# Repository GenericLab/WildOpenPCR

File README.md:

# WildOpenPCR
DIY derivate of the OpenPCR Project.
Original design of OpenPCR by Tito Jakowski and Jeff Perfutto: http://openpcr.org/

For more info see: http://wlu18www30.webland.ch/wiki/Wild_OpenPCR

and: http://www.gaudi.ch/GaudiLabs/?page_id=328

All OpenPCR software, design files and instructions are licensed under the GNU GPLv3.

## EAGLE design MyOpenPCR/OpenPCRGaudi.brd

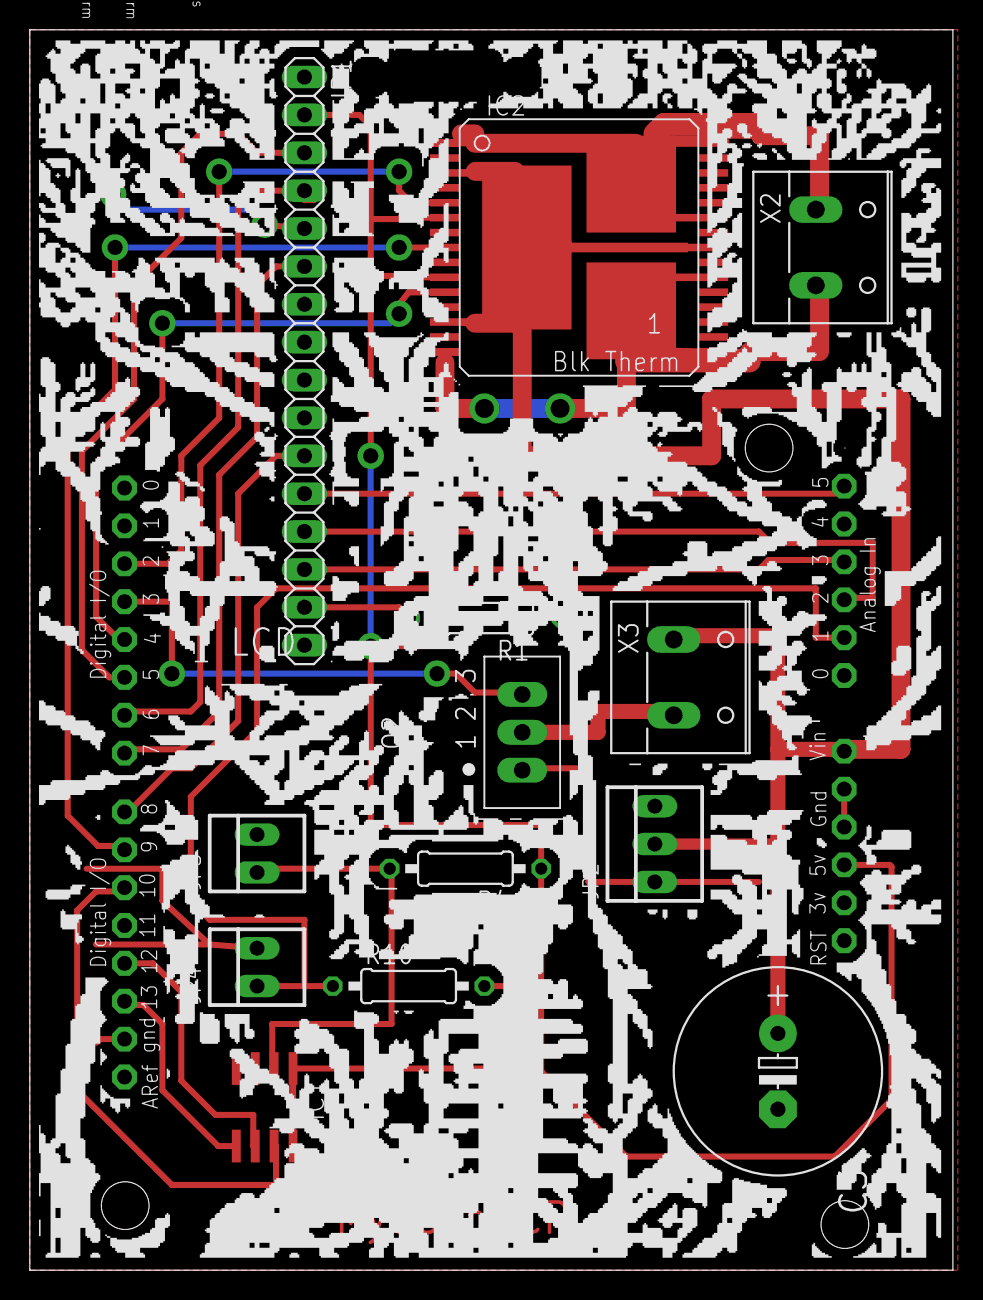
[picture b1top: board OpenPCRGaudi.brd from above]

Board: 2 copper layers, 61.9 x 83.2 mm, 14 parts (0 on the bottom side), 23 nets.

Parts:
C3: E5-13
IC1: MCP3551SN; SO-08
IC2: VNH3SP30_2; MULTIPOWERSO-30
JP1: 1X16
JP2: 22-23-2031
JP3, JP4: 22-23-2021
Q2: BSS97; TO202
R1, R4, R10: 0207/10
U$3: ARDUINODUEMILANOVE; ARDUINO
X2, X3: W237-132

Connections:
+5VREG: IC1.1, IC1.8, IC2.6, IC2.10, JP1.2, R1.1, R4.1, R10.2, U$3.5V
+12V1: C3.+, IC2.3, IC2.13, IC2.23, IC2.VCC, IC2.VCC@1, JP2.2, U$3.VIN, X3.1
GND1: C3.-, IC1.3, IC1.4, IC2.18, IC2.19, IC2.20, IC2.26, IC2.27, IC2.28, JP1.1, JP1.5, JP1.16, JP2.1, JP3.2, JP4.2, Q2.1, U$3.GND, U$3.GND1, U$3.GND2
unnamed: JP1.3, U$3.D5
unnamed: JP1.4, U$3.D6
unnamed: JP1.14, U$3.A3
unnamed: JP1.15, R1.2
unnamed: Q2.3, U$3.D3
unnamed: JP1.13, U$3.A2
unnamed: JP1.6, U$3.D7
unnamed: JP1.12, U$3.A5
unnamed: IC1.5, U$3.D13
unnamed: Q2.2, X3.2
unnamed: JP1.11, U$3.D8
unnamed: IC1.2, JP3.1, R4.2
unnamed: IC2.1, IC2.25, IC2.30, IC2.GND, IC2.OUTA, X2.1
unnamed: IC1.6, U$3.D12
unnamed: IC1.7, U$3.D10
unnamed: IC2.8, U$3.D9
unnamed: IC2.11, U$3.D4
unnamed: IC2.15, IC2.16, IC2.21, IC2.OUTB, IC2.SS, X2.2
unnamed: IC2.5, U$3.D2
unnamed: JP4.1, R10.1, U$3.A1

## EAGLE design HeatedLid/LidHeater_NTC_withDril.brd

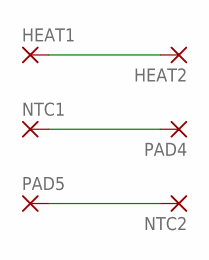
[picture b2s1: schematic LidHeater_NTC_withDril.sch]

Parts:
HEAT1, HEAT2: SMD5; SMD2,54-5,08
NTC1, NTC2: SMD5; SMD2,54-5,08
PAD4, PAD5: SMD5; SMD2,54-5,08

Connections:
unnamed: HEAT1.1, HEAT2.1
unnamed: NTC1.1, PAD4.1
unnamed: NTC2.1, PAD5.1

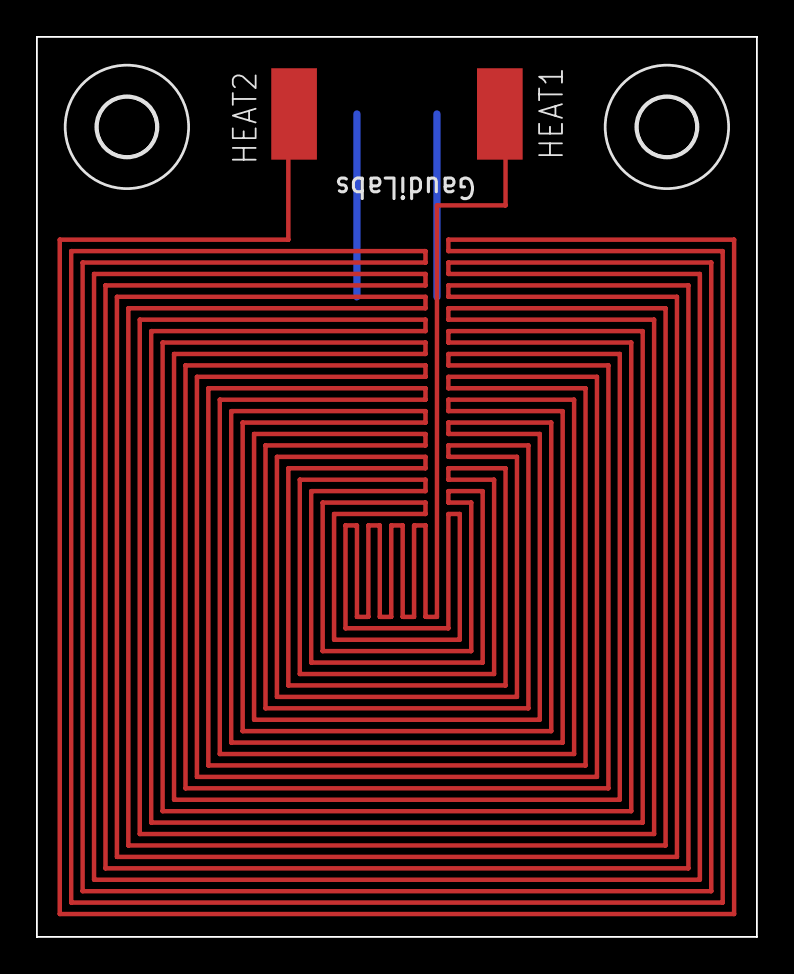
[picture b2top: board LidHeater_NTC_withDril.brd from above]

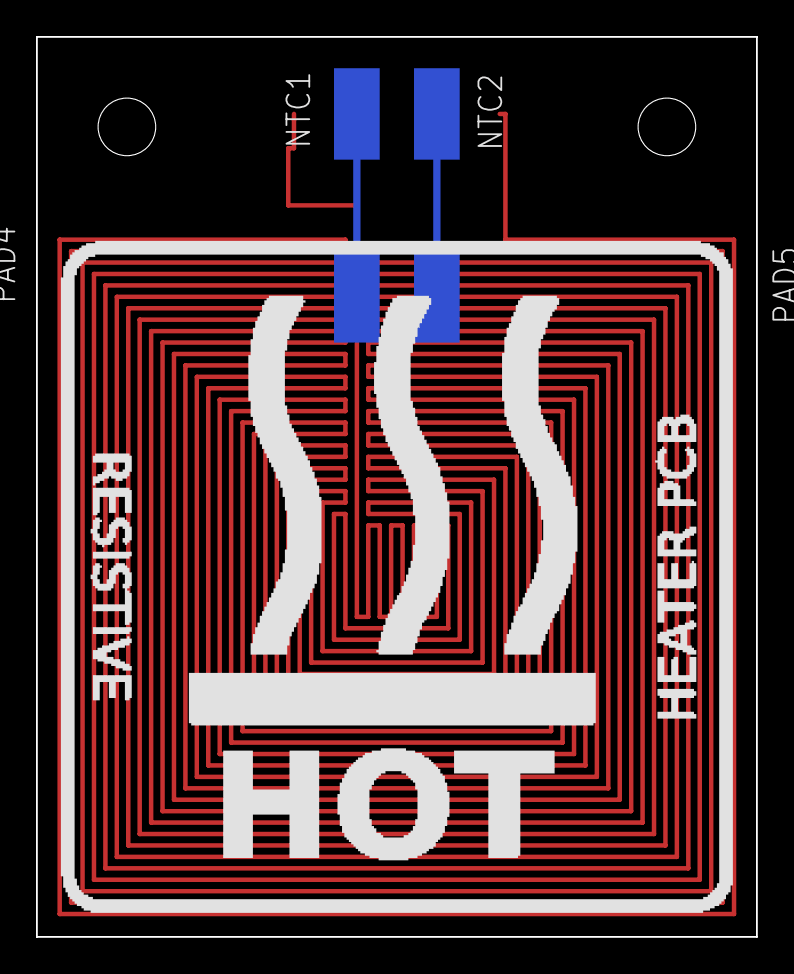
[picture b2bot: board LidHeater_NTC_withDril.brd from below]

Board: 2 copper layers, 40.0 x 50.0 mm, 8 parts (4 on the bottom side), 3 nets.

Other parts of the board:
U$1, U$2: 3,2

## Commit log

2017-02-08 first upload wildOpenPCR
2017-02-08 updated readme with credits
2017-02-08 added photos
    and links
2017-02-15 added MEGA16U2 HEX
2017-02-24 fixed an error on the PCB and added new Code
    for two line LCD and different temp sensor.
2017-03-16 added compiled .hex files
